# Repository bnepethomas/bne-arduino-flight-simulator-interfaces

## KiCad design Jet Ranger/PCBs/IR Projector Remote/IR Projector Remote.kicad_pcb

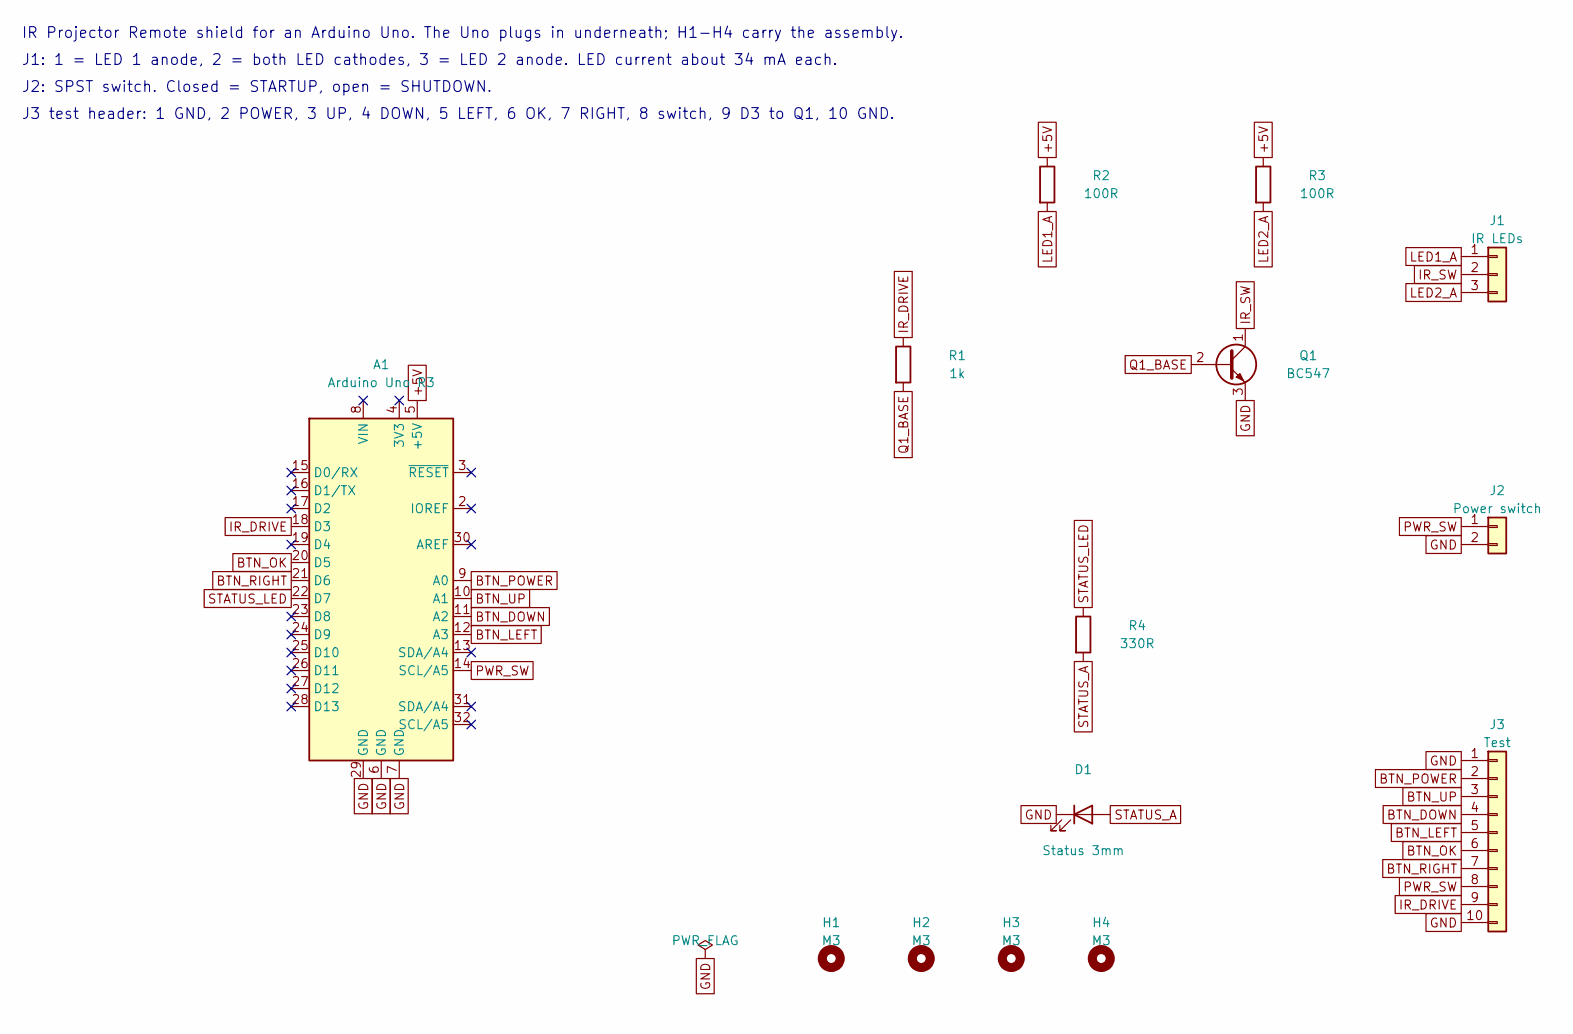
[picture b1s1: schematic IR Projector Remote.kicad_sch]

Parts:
A1: Arduino Uno R3; Arduino_UNO_Shield
D1: Status 3mm; LED_D3.0mm
H1, H2, H3, H4: M3; MountingHole_3.2mm_M3
J1: IR LEDs; Molex_KK-254_AE-6410-03A_1x03_P2.54mm_Vertical
J2: Power switch; Molex_KK-254_AE-6410-02A_1x02_P2.54mm_Vertical
J3: Test; PinHeader_1x10_P2.54mm_Vertical
Q1: BC547; TO-92_Inline_Wide
R1: 1k; R_Axial_DIN0207_L6.3mm_D2.5mm_P10.16mm_Horizontal
R2, R3: 100R; R_Axial_DIN0207_L6.3mm_D2.5mm_P10.16mm_Horizontal
R4: 330R; R_Axial_DIN0207_L6.3mm_D2.5mm_P10.16mm_Horizontal

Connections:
+5V: A1.5 (+5V), R2.1, R3.1
BTN_DOWN: A1.11 (A2), J3.4
BTN_LEFT: A1.12 (A3), J3.5
BTN_OK: A1.20 (D5), J3.6
BTN_POWER: A1.9 (A0), J3.2
BTN_RIGHT: A1.21 (D6), J3.7
BTN_UP: A1.10 (A1), J3.3
GND: A1.6 (GND), A1.7 (GND), A1.29 (GND), D1.1 (K), J2.2, J3.1, J3.10, Q1.3 (E)
IR_DRIVE: A1.18 (D3), J3.9, R1.1
IR_SW: J1.2, Q1.1 (C)
LED1_A: J1.1, R2.2
LED2_A: J1.3, R3.2
PWR_SW: A1.14 (SCL/A5), J2.1, J3.8
Q1_BASE: Q1.2 (B), R1.2
STATUS_A: D1.2 (A), R4.2
STATUS_LED: A1.22 (D7), R4.1

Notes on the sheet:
IR Projector Remote shield for an Arduino Uno. The Uno plugs in underneath; H1-H4 carry the assembly.
J1: 1 = LED 1 anode, 2 = both LED cathodes, 3 = LED 2 anode. LED current about 34 mA each.
J2: SPST switch. Closed = STARTUP, open = SHUTDOWN.
J3 test header: 1 GND, 2 POWER, 3 UP, 4 DOWN, 5 LEFT, 6 OK, 7 RIGHT, 8 switch, 9 D3 to Q1, 10 GND.

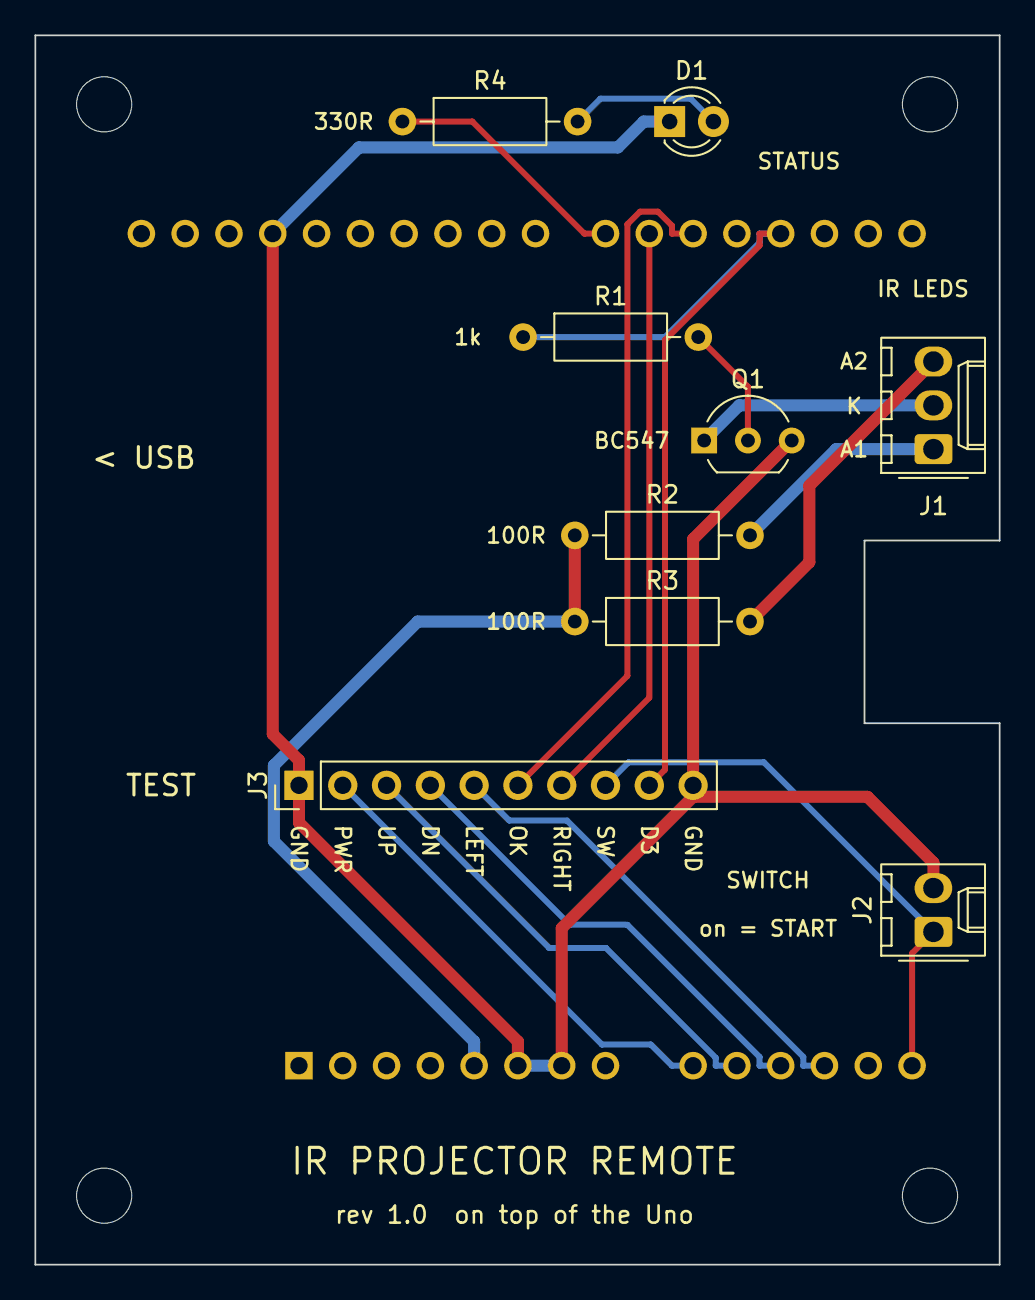
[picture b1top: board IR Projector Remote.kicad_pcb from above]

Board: 2 copper layers, 55.9 x 71.3 mm, 14 parts (0 on the bottom side), 16 nets.

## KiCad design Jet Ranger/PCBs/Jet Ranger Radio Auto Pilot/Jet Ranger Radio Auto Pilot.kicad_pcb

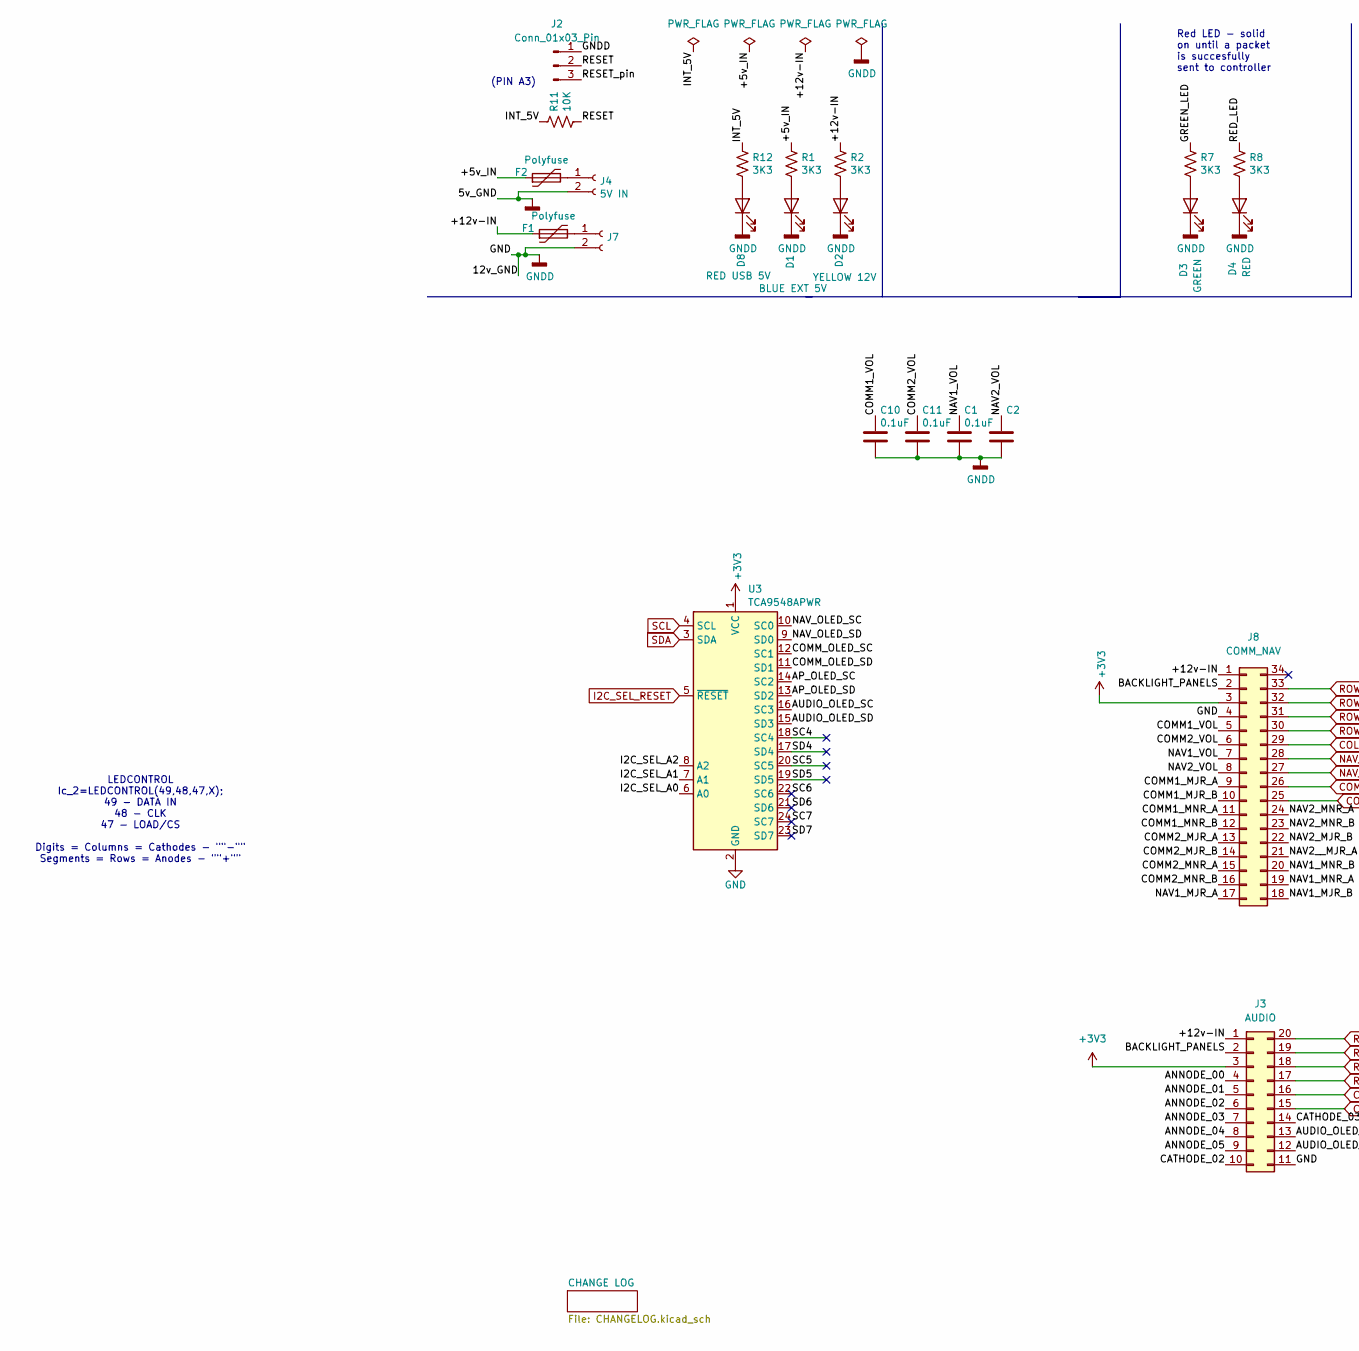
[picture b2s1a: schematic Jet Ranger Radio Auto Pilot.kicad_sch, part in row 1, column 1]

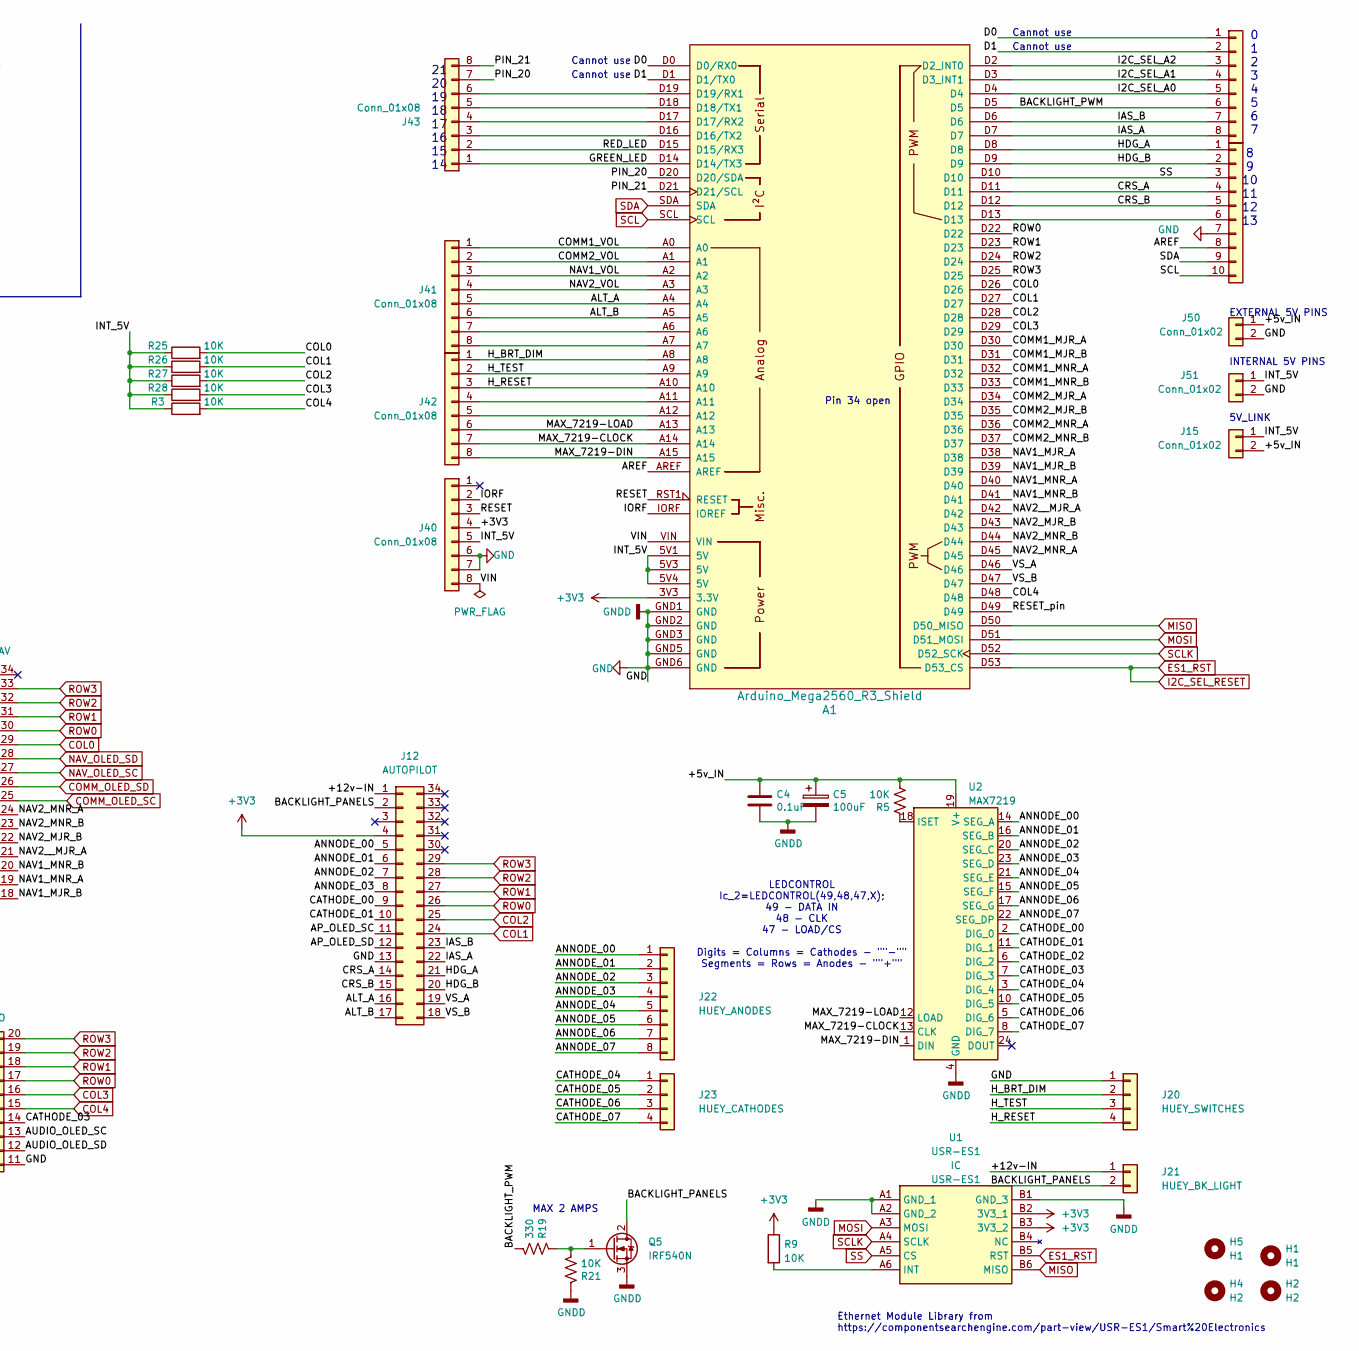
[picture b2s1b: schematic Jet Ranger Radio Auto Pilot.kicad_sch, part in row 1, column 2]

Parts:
A1: Arduino_Mega2560_R3_Shield
C1, C2, C4, C10, C11: 0.1uF; C_Disc_D3.0mm_W2.0mm_P2.50mm
C5: 100uF; C_Radial_D8.0mm_H7.0mm_P3.50mm
D1: BLUE EXT 5V; LED_D3.0mm
D2: YELLOW 12V; LED_D3.0mm
D3: GREEN; LED_D3.0mm
D4: RED; LED_D3.0mm
D8: RED USB 5V; LED_D3.0mm
F1, F2: Polyfuse; Fuse_Littelfuse_395Series
H1, H5: H1; MountingHole_3.2mm_M3
H2, H4: H2; MountingHole_3.2mm_M3
J2: Conn_01x03_Pin; PinHeader_1x03_P2.54mm_Vertical
J3: AUDIO; IDC-Header_2x10_P2.54mm_Vertical
J4: 5V IN; BarrelJack_Horizontal
J7: STEPPER IN 12-20VDC; BarrelJack_Horizontal
J8: COMM_NAV; IDC-Header_2x17_P2.54mm_Vertical
J12: AUTOPILOT; IDC-Header_2x17_P2.54mm_Vertical
J15, J50, J51: Conn_01x02; PinHeader_1x02_P2.54mm_Vertical
J20: HUEY_SWITCHES; Molex_KK-254_AE-6410-04A_1x04_P2.54mm_Vertical
J21: HUEY_BK_LIGHT; Molex_KK-254_AE-6410-02A_1x02_P2.54mm_Vertical
J22: HUEY_ANODES; Molex_KK-254_AE-6410-08A_1x08_P2.54mm_Vertical
J23: HUEY_CATHODES; Molex_KK-254_AE-6410-04A_1x04_P2.54mm_Vertical
J40, J41, J42, J43, J44: Conn_01x08; PinHeader_1x08_P2.54mm_Vertical
J45: Conn_01x10; PinHeader_1x10_P2.54mm_Vertical
Q5: IRF540N; TO-220-3_Vertical
R1, R2, R7, R8, R12: 3K3; R_Axial_DIN0207_L6.3mm_D2.5mm_P2.54mm_Vertical
R3, R5, R9, R11, R21, R25, R26, R27, R28: 10K; R_Axial_DIN0207_L6.3mm_D2.5mm_P2.54mm_Vertical
R19: 330; R_Axial_DIN0207_L6.3mm_D2.5mm_P2.54mm_Vertical
U1: USR-ES1; USRES1; Manufacturer_Part_Number USR-ES1
U2: MAX7219; DIP-24_W7.62mm_LongPads
U3: TCA9548APWR; AllieExpress_TCA9548A

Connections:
+3V3: A1.3V3 (3.3V), J3.3, J8.3, J12.4, J40.4, R9.1, U1.B2 (3V3_1), U1.B3 (3V3_2), U3.1 (VCC)
/+5v_IN: C4.1, C5.1, F2.1, J15.2, J50.1, R1.1, R5.2, U2.19 (V+)
/+12v-IN: F1.1, J3.1, J8.1, J12.1, J21.1, R2.1
/ALT_A: A1.A4, J12.16, J41.5
/ALT_B: A1.A5, J12.17, J41.6
/ANNODE_00: J3.4, J12.5, J22.1, U2.14 (SEG_A)
/ANNODE_01: J3.5, J12.6, J22.2, U2.16 (SEG_B)
/ANNODE_02: J3.6, J12.7, J22.3, U2.20 (SEG_C)
/ANNODE_03: J3.7, J12.8, J22.4, U2.23 (SEG_D)
/ANNODE_04: J3.8, J22.5, U2.21 (SEG_E)
/ANNODE_05: J3.9, J22.6, U2.15 (SEG_F)
/ANNODE_06: J22.7, U2.17 (SEG_G)
/ANNODE_07: J22.8, U2.22 (SEG_DP)
/AP_OLED_SC: J12.11, U3.14 (SC2)
/AP_OLED_SD: J12.12, U3.13 (SD2)
/AREF: A1.AREF, J45.8
/AUDIO_OLED_SC: J3.13, U3.16 (SC3)
/AUDIO_OLED_SD: J3.12, U3.15 (SD3)
/BACKLIGHT_PANELS: J3.2, J8.2, J12.2, J21.2, Q5.2 (D)
/BACKLIGHT_PWM: A1.D5, J44.6, R19.2
/CATHODE_00: J12.9, U2.2 (DIG_0)
/CATHODE_01: J12.10, U2.11 (DIG_1)
/CATHODE_02: J3.10, U2.6 (DIG_2)
/CATHODE_03: J3.14, U2.7 (DIG_3)
/CATHODE_04: J23.1, U2.3 (DIG_4)
/CATHODE_05: J23.2, U2.10 (DIG_5)
/CATHODE_06: J23.3, U2.5 (DIG_6)
/CATHODE_07: J23.4, U2.8 (DIG_7)
/COMM1_MJR_A: A1.D30, J8.9
/COMM1_MJR_B: A1.D31, J8.10
/COMM1_MNR_A: A1.D32, J8.11
/COMM1_MNR_B: A1.D33, J8.12
/COMM1_VOL: A1.A0, C10.1, J8.5, J41.1
/COMM2_MJR_A: A1.D34, J8.13
/COMM2_MJR_B: A1.D35, J8.14
/COMM2_MNR_A: A1.D36, J8.15
/COMM2_MNR_B: A1.D37, J8.16
/COMM2_VOL: A1.A1, C11.1, J8.6, J41.2
/CRS_A: A1.D11, J12.14, J45.4
/CRS_B: A1.D12, J12.15, J45.5
/D0: A1.D0 (D0/RX0), J44.1
/D1: A1.D1 (D1/TX0), J44.2
/GREEN_LED: A1.D14 (D14/TX3), J43.1, R7.1
/HDG_A: A1.D8, J12.21, J45.1
/HDG_B: A1.D9, J12.20, J45.2
/H_BRT_DIM: A1.A8, J20.2, J42.1
/H_RESET: A1.A10, J20.4, J42.3
/H_TEST: A1.A9, J20.3, J42.2
/I2C_SEL_A0: A1.D4, J44.5, U3.6 (A0)
/I2C_SEL_A1: A1.D3 (D3_INT1), J44.4, U3.7 (A1)
/I2C_SEL_A2: A1.D2 (D2_INT0), J44.3, U3.8 (A2)
/IAS_A: A1.D7, J12.22, J44.8
/IAS_B: A1.D6, J12.23, J44.7
/INT_5V: A1.5V1 (5V), A1.5V3 (5V), A1.5V4 (5V), J15.1, J40.5, J51.1, R3.1, R11.1, R12.1, R25.1, R26.1, R27.1, R28.1
/IORF: A1.IORF (IOREF), J40.2
/MAX_7219-CLOCK: A1.A14, J42.7, U2.13 (CLK)
/MAX_7219-DIN: A1.A15, J42.8, U2.1 (DIN)
/MAX_7219-LOAD: A1.A13, J42.6, U2.12 (LOAD)
/NAV1_MJR_A: A1.D38, J8.17
/NAV1_MJR_B: A1.D39, J8.18
/NAV1_MNR_A: A1.D40, J8.19
/NAV1_MNR_B: A1.D41, J8.20
/NAV1_VOL: A1.A2, C1.1, J8.7, J41.3
/NAV2_MJR_B: A1.D43, J8.22
/NAV2_MNR_A: A1.D45, J8.24
/NAV2_MNR_B: A1.D44, J8.23
/NAV2_VOL: A1.A3, C2.1, J8.8, J41.4
/NAV2__MJR_A: A1.D42, J8.21
/PIN_20: A1.D20 (D20/SDA), J43.7
/PIN_21: A1.D21 (D21/SCL), J43.8
/RED_LED: A1.D15 (D15/RX3), J43.2, R8.1
/RESET: A1.RST1 (RESET), J2.2, J40.3, R11.2
/RESET_pin: A1.D49, J2.3
/SC4: U3.18 (SC4)
/SC5: U3.20 (SC5)
/SC6: U3.22 (SC6)
/SC7: U3.24 (SC7)
/SD4: U3.17 (SD4)
/SD5: U3.19 (SD5)
/SD6: U3.21 (SD6)
/SD7: U3.23 (SD7)
/VIN: A1.VIN, J40.8
/VS_A: A1.D46, J12.19
/VS_B: A1.D47, J12.18
COL0: A1.D26, J8.29, R25.2
COL1: A1.D27, J12.24, R26.2
COL2: A1.D28, J12.25, R27.2
COL3: A1.D29, J3.16, R28.2
COL4: A1.D48, J3.15, R3.2
COMM_OLED_SC: J8.25, U3.12 (SC1)
COMM_OLED_SD: J8.26, U3.11 (SD1)
ES1_RST: A1.D53 (D53_CS), U1.B5 (RST), U3.5 (~RESET)
GND: A1.GND1 (GND), A1.GND2 (GND), A1.GND3 (GND), A1.GND5 (GND), A1.GND6 (GND), C1.2, C2.2, C4.2, C5.2, C10.2, C11.2, D1.1 (K), D2.1 (K), D3.1 (K), D4.1 (K), D8.1 (K), J2.1, J3.11, J4.2, J7.2, J8.4, J12.13, J20.1, J40.6, J40.7, J45.7, J50.2, J51.2, Q5.3 (S), R21.1, U1.A1 (GND_1), U1.A2 (GND_2), U1.B1 (GND_3), U2.4 (GND), U2.9 (GND), U3.2 (GND)
MISO: A1.D50 (D50_MISO), U1.B6 (MISO)
MOSI: A1.D51 (D51_MOSI), U1.A3 (MOSI)
NAV_OLED_SC: J8.27, U3.10 (SC0)
NAV_OLED_SD: J8.28, U3.9 (SD0)
unnamed: A1.D16 (D16/TX2), J43.3
unnamed: A1.D17 (D17/RX2), J43.4
unnamed: A1.D18 (D18/TX1), J43.5
unnamed: A1.D19 (D19/RX1), J43.6
unnamed: D1.2 (A), R1.2
unnamed: D2.2 (A), R2.2
unnamed: D3.2 (A), R7.2
unnamed: D4.2 (A), R8.2
unnamed: D8.2 (A), R12.2
unnamed: F2.2, J4.1
unnamed: F1.2, J7.1
unnamed: A1.A6, J41.7
unnamed: A1.A7, J41.8
unnamed: A1.A11, J42.4
unnamed: A1.A12, J42.5
unnamed: A1.D13, J45.6
unnamed: Q5.1 (G), R19.1, R21.2
unnamed: R9.2, U1.A6 (INT)
unnamed: R5.1, U2.18 (ISET)
ROW0: A1.D22, J3.17, J8.30, J12.26
ROW1: A1.D23, J3.18, J8.31, J12.27
ROW2: A1.D24, J3.19, J8.32, J12.28
ROW3: A1.D25, J3.20, J8.33, J12.29
SCL: A1.SCL, J45.10, U3.4 (SCL)
SCLK: A1.D52 (D52_SCK), U1.A4 (SCLK)
SDA: A1.SDA, J45.9, U3.3 (SDA)
SS: A1.D10, J45.3, U1.A5 (CS)

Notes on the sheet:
Pin 34 open
MAX 2 AMPS
INTERNAL 5V PINS
Ethernet Module Library from https://componentsearchengine.com/part-view/USR-ES1/Smart%20Electronics
LEDCONTROL Ic_2=LEDCONTROL(49,48,47,X); 49 - DATA IN 48 - CLK 47 - LOAD/CS Digits = Columns = Cathodes - ""-"" Segments = Rows = Anodes - ""+""
Cannot use
(PIN A3)
0 1 2 3 4 5 6 7
Red LED - solid on until a packet is succesfully sent to controller
5V_LINK
21 20 19 18 17 16 15 14
EXTERNAL 5V PINS
8 9 10 11 12 13

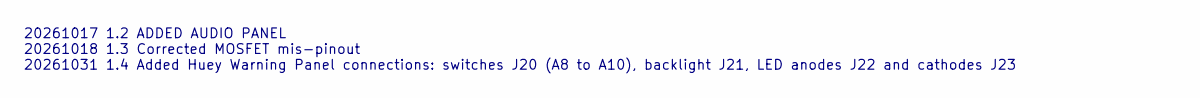
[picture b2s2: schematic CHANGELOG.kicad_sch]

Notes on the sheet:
20261017 1.2 ADDED AUDIO PANEL 20261018 1.3 Corrected MOSFET mis-pinout 20261031 1.4 Added Huey Warning Panel connections: switches J20 (A8 to A10), backlight J21, LED anodes J22 and cathodes J23

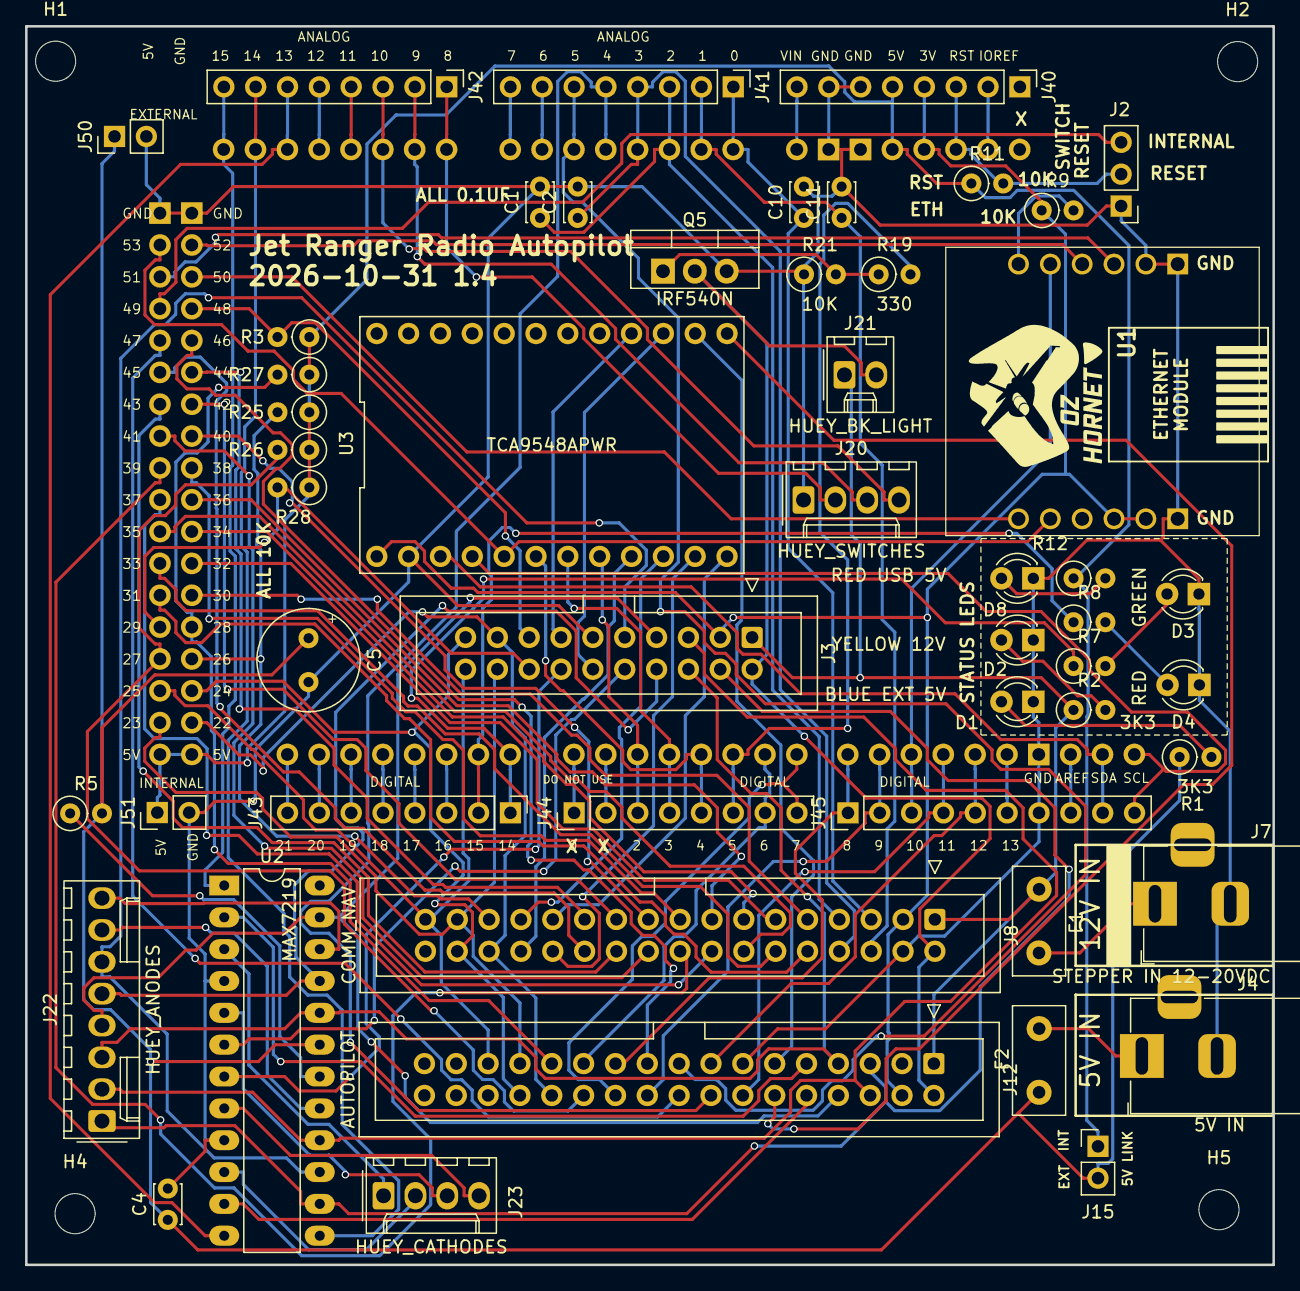
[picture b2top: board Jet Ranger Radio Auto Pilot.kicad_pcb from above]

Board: 2 copper layers, 99.5 x 98.8 mm, 56 parts (0 on the bottom side), 116 nets.

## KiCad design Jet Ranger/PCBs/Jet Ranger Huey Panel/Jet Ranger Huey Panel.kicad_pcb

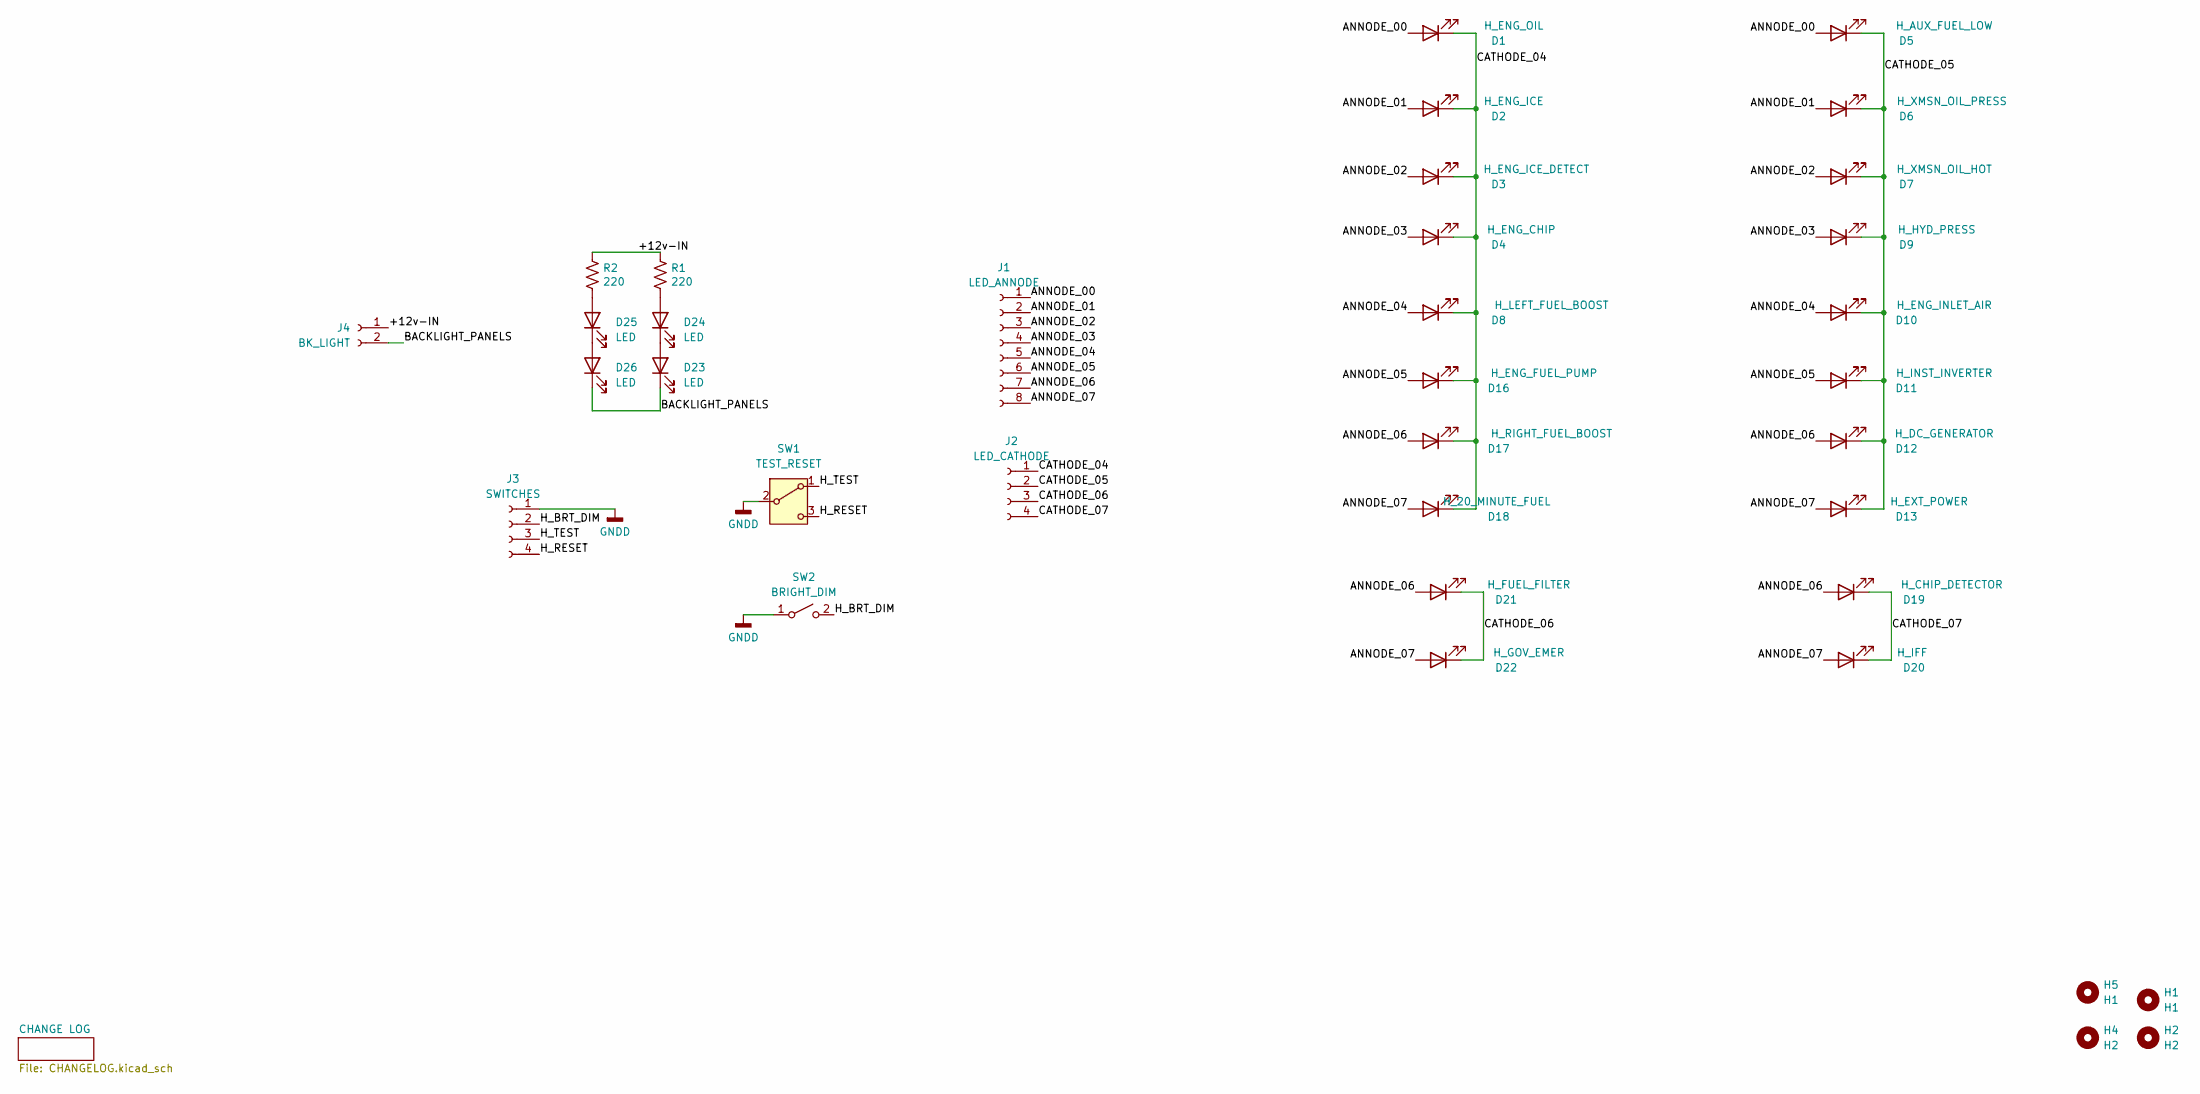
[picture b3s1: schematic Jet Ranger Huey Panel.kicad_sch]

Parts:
D1: H_ENG_OIL; LED_D3.0mm
D2: H_ENG_ICE; LED_D3.0mm
D3: H_ENG_ICE_DETECT; LED_D3.0mm
D4: H_ENG_CHIP; LED_D3.0mm
D5: H_AUX_FUEL_LOW; LED_D3.0mm
D6: H_XMSN_OIL_PRESS; LED_D3.0mm
D7: H_XMSN_OIL_HOT; LED_D3.0mm
D8: H_LEFT_FUEL_BOOST; LED_D3.0mm
D9: H_HYD_PRESS; LED_D3.0mm
D10: H_ENG_INLET_AIR; LED_D3.0mm
D11: H_INST_INVERTER; LED_D3.0mm
D12: H_DC_GENERATOR; LED_D3.0mm
D13: H_EXT_POWER; LED_D3.0mm
D16: H_ENG_FUEL_PUMP; LED_D3.0mm
D17: H_RIGHT_FUEL_BOOST; LED_D3.0mm
D18: H_20_MINUTE_FUEL; LED_D3.0mm
D19: H_CHIP_DETECTOR; LED_D3.0mm
D20: H_IFF; LED_D3.0mm
D21: H_FUEL_FILTER; LED_D3.0mm
D22: H_GOV_EMER; LED_D3.0mm
D23, D24, D25, D26: LED; LED_D3.0mm
H1, H5: H1; MountingHole_3.2mm_M3
H2, H4: H2; MountingHole_3.2mm_M3
J1: LED_ANNODE; Molex_KK-254_AE-6410-08A_1x08_P2.54mm_Vertical
J2: LED_CATHODE; Molex_KK-254_AE-6410-04A_1x04_P2.54mm_Vertical
J3: SWITCHES; Molex_KK-254_AE-6410-04A_1x04_P2.54mm_Vertical
J4: BK_LIGHT; Molex_KK-254_AE-6410-02A_1x02_P2.54mm_Vertical
R1, R2: 220; R_Axial_DIN0207_L6.3mm_D2.5mm_P2.54mm_Vertical
SW1: TEST_RESET; Molex_KK-254_AE-6410-03A_1x03_P2.54mm_Vertical
SW2: BRIGHT_DIM; Molex_KK-254_AE-6410-02A_1x02_P2.54mm_Vertical

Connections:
/+12v-IN: J4.1, R1.1, R2.1
/ANNODE_00: D1.2 (A), D5.2 (A), J1.1
/ANNODE_01: D2.2 (A), D6.2 (A), J1.2
/ANNODE_02: D3.2 (A), D7.2 (A), J1.3
/ANNODE_03: D4.2 (A), D9.2 (A), J1.4
/ANNODE_04: D8.2 (A), D10.2 (A), J1.5
/ANNODE_05: D11.2 (A), D16.2 (A), J1.6
/ANNODE_06: D12.2 (A), D17.2 (A), D19.2 (A), D21.2 (A), J1.7
/ANNODE_07: D13.2 (A), D18.2 (A), D20.2 (A), D22.2 (A), J1.8
/BACKLIGHT_PANELS: D23.1 (K), D26.1 (K), J4.2
/CATHODE_04: D1.1 (K), D2.1 (K), D3.1 (K), D4.1 (K), D8.1 (K), D16.1 (K), D17.1 (K), D18.1 (K), J2.1
/CATHODE_05: D5.1 (K), D6.1 (K), D7.1 (K), D9.1 (K), D10.1 (K), D11.1 (K), D12.1 (K), D13.1 (K), J2.2
/CATHODE_06: D21.1 (K), D22.1 (K), J2.3
/CATHODE_07: D19.1 (K), D20.1 (K), J2.4
/H_BRT_DIM: J3.2, SW2.2 (B)
/H_RESET: J3.4, SW1.3 (C)
/H_TEST: J3.3, SW1.1 (A)
GNDD: J3.1, SW1.2 (B), SW2.1 (A)
unnamed: D23.2 (A), D24.1 (K)
unnamed: D24.2 (A), R1.2
unnamed: D25.2 (A), R2.2
unnamed: D25.1 (K), D26.2 (A)

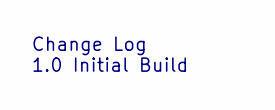
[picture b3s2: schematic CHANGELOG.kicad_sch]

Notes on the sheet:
Change Log 1.0 Initial Build

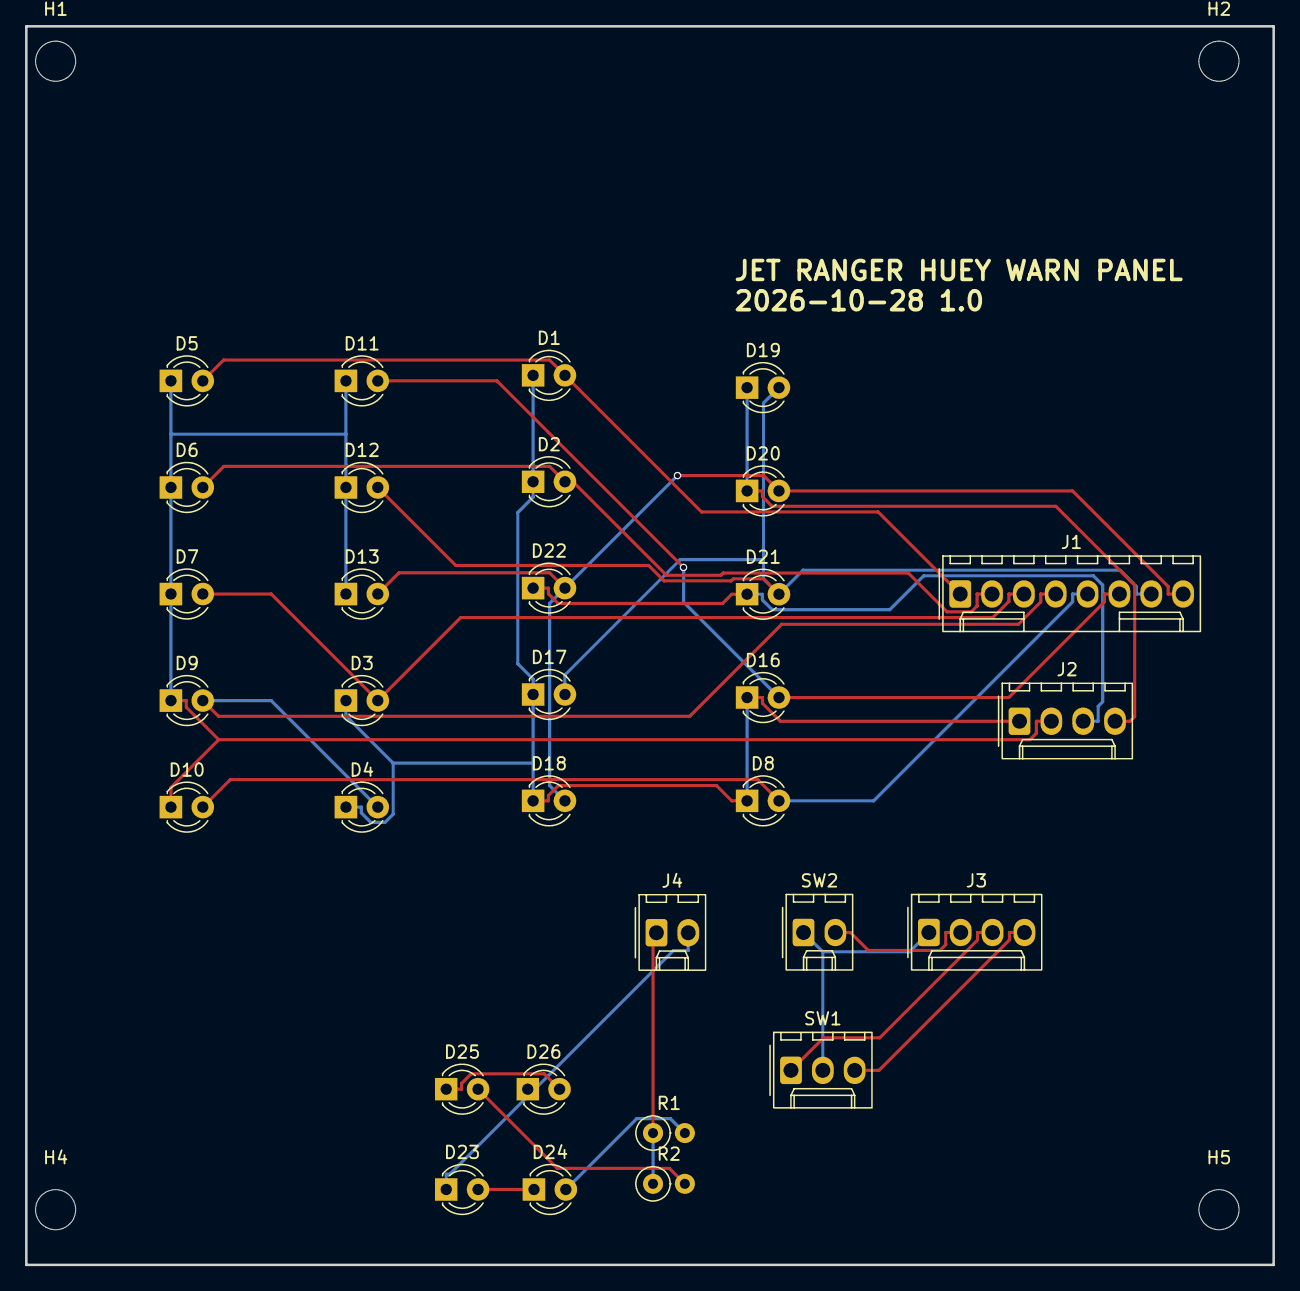
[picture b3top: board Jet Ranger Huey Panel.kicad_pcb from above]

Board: 2 copper layers, 99.5 x 98.8 mm, 36 parts (0 on the bottom side), 22 nets.

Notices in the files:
Jet Ranger/PCBs/Jet Ranger 13 Stepper/Jet Ranger 13 Stepper.kicad_pcb:
© OZ HORNET
